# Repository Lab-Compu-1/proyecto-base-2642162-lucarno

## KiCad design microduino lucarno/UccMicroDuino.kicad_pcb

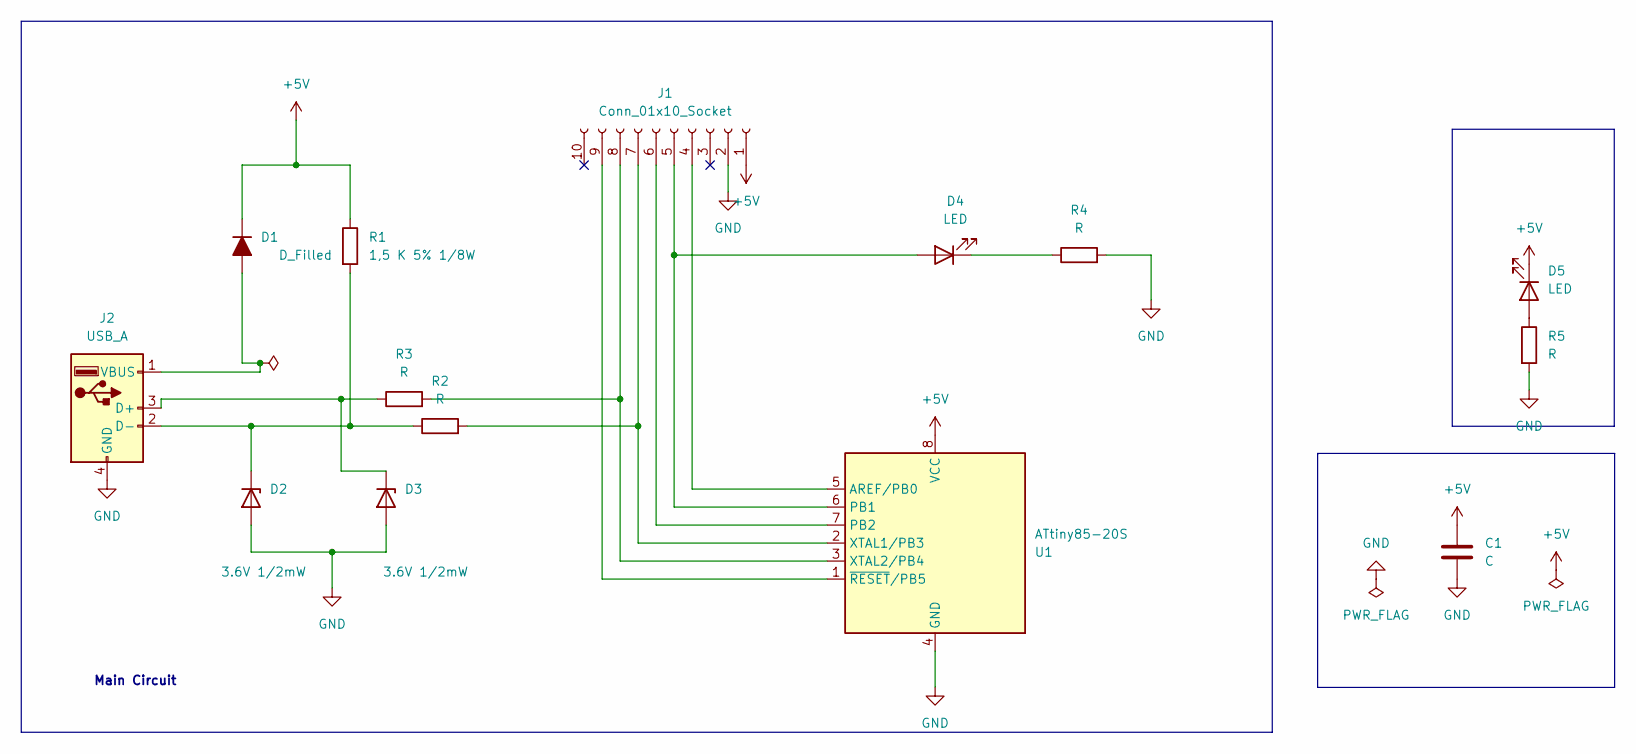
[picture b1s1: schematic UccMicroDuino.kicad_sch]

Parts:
C1: C; C_0805_2012Metric_Pad1.18x1.45mm_HandSolder
D1: D_Filled; D_MiniMELF
D2, D3: 3.6V 1/2mW; D_SOD-123
D4, D5: LED; ledSMD
J1: Conn_01x10_Socket; PinHeader_1x10_P2.54mm_Vertical
J2: USB_A; USB_A_UCC
R1: 1,5 K 5% 1/8W; R_0805_2012Metric_Pad1.20x1.40mm_HandSolder
R2, R3, R4, R5: R; R_0805_2012Metric_Pad1.20x1.40mm_HandSolder
U1: ATtiny85-20S; SOIC-8W_5.3x5.3mm_P1.27mm

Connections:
+5V: C1.1, D1.1 (K), D5.1 (K), J1.1, R1.1, U1.8 (VCC)
GND: C1.2, D2.2 (A), D3.2 (A), J1.2, J2.4 (GND), R4.2, R5.2, U1.4 (GND)
unnamed: D1.2 (A), J2.1 (VBUS)
unnamed: D2.1 (K), J2.2 (D-), R1.2, R2.1
unnamed: D3.1 (K), J2.3 (D+), R3.1
unnamed: D4.2 (A), J1.5, U1.6 (PB1)
unnamed: D4.1 (K), R4.1
unnamed: D5.2 (A), R5.1
unnamed: J1.4, U1.5 (AREF/PB0)
unnamed: J1.6, U1.7 (PB2)
unnamed: J1.7, R2.2, U1.2 (XTAL1/PB3)
unnamed: J1.8, R3.2, U1.3 (XTAL2/PB4)
unnamed: J1.9, U1.1 (~RESET/PB5)

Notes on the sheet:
Main Circuit

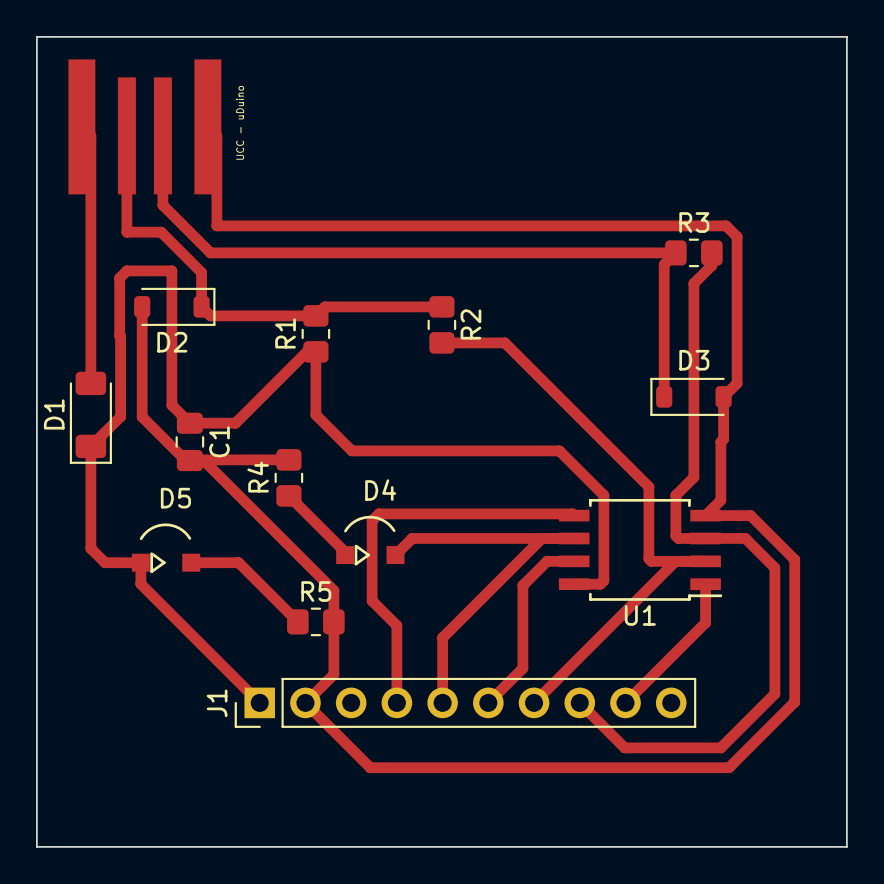
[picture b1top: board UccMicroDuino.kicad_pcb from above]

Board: 2 copper layers, 45.0 x 45.0 mm, 14 parts (0 on the bottom side), 13 nets.

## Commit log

2026-03-30 GitHub Classroom Feedback
2026-03-30 Setting up GitHub Classroom Feedback
2026-05-31 Cambio realizado en README
2026-06-01 mi primer versionado con git
